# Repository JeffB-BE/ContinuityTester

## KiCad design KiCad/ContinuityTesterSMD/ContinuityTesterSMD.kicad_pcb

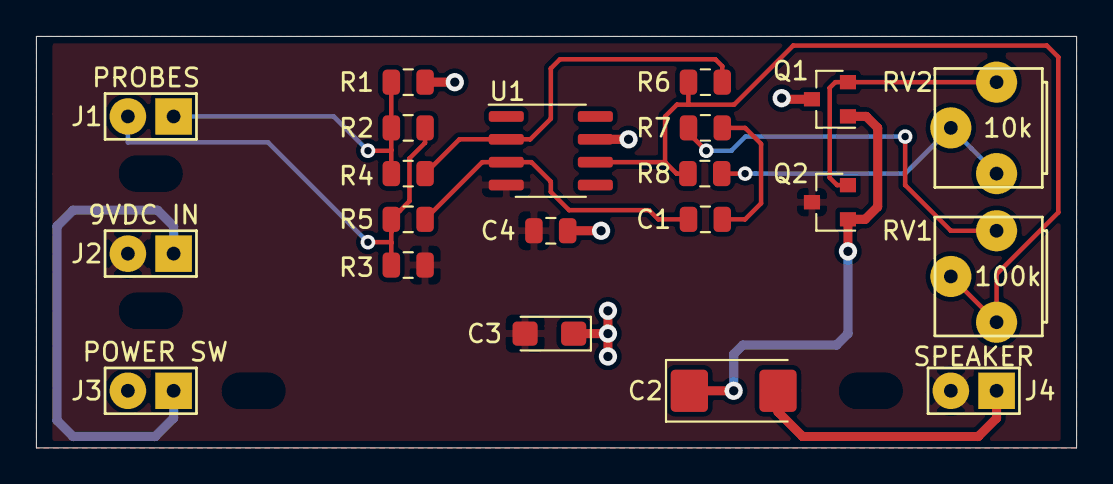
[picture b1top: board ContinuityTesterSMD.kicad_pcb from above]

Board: 2 copper layers, 57.8 x 22.9 mm, 21 parts (0 on the bottom side), 14 nets.

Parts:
C1: 1nF; C_0805_2012Metric
C2: 15uF; CP_EIA-6032-28_Kemet-C
C3: 10uF; CP_EIA-3216-18_Kemet-A
C4: .1uF; C_0805_2012Metric
J1: PROBES; SolderWirePad_1x02_Pitch100mil_Drill30mil
J2: 9VDC IN; SolderWirePad_1x02_Pitch100mil_Drill30mil
J3: POWER SW; SolderWirePad_1x02_Pitch100mil_Drill30mil
J4: SPEAKER; SolderWirePad_1x02_Pitch100mil_Drill30mil
Q1: 2N4401; SOT-23
Q2: 2N4403; SOT-23
R1, R3, R4, R5: 10k; R_0805_2012Metric
R2: 100R; R_0805_2012Metric
R6: 4M6; R_0805_2012Metric
R7: 49k9; R_0805_2012Metric
R8: 2k; R_0805_2012Metric
RV1: 100k; Bourns_3329S_Vertical
RV2: 10k; Bourns_3329S_Vertical
U1: uA741CP; SOIC-8_3.9x4.9mm_P1.27mm

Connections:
+9V: C3.1, C4.2, J3.2, Q1.3, R1.1, U1.7
GND: C3.2, C4.1, J2.2, J4.2, Q2.3, R3.2, U1.4
unnamed: C1.1, R7.2
unnamed: C1.2, R5.1, U1.3
unnamed: C2.1, Q1.1, Q2.1
unnamed: C2.2, J4.1
unnamed: J1.1, R1.2, R2.1, R4.2
unnamed: J1.2, R2.2, R3.1, R5.2
unnamed: J2.1, J3.1
unnamed: Q1.2, Q2.2, RV2.3
unnamed: R4.1, R6.2, U1.2
unnamed: R6.1, R8.2, RV1.1, RV1.2, U1.6
unnamed: R7.1, RV1.3
unnamed: R8.1, RV2.1, RV2.2

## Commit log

2020-05-09 Initial project upload
2020-05-09 update gitignore
2020-05-09 Added custom 3D models to repository
